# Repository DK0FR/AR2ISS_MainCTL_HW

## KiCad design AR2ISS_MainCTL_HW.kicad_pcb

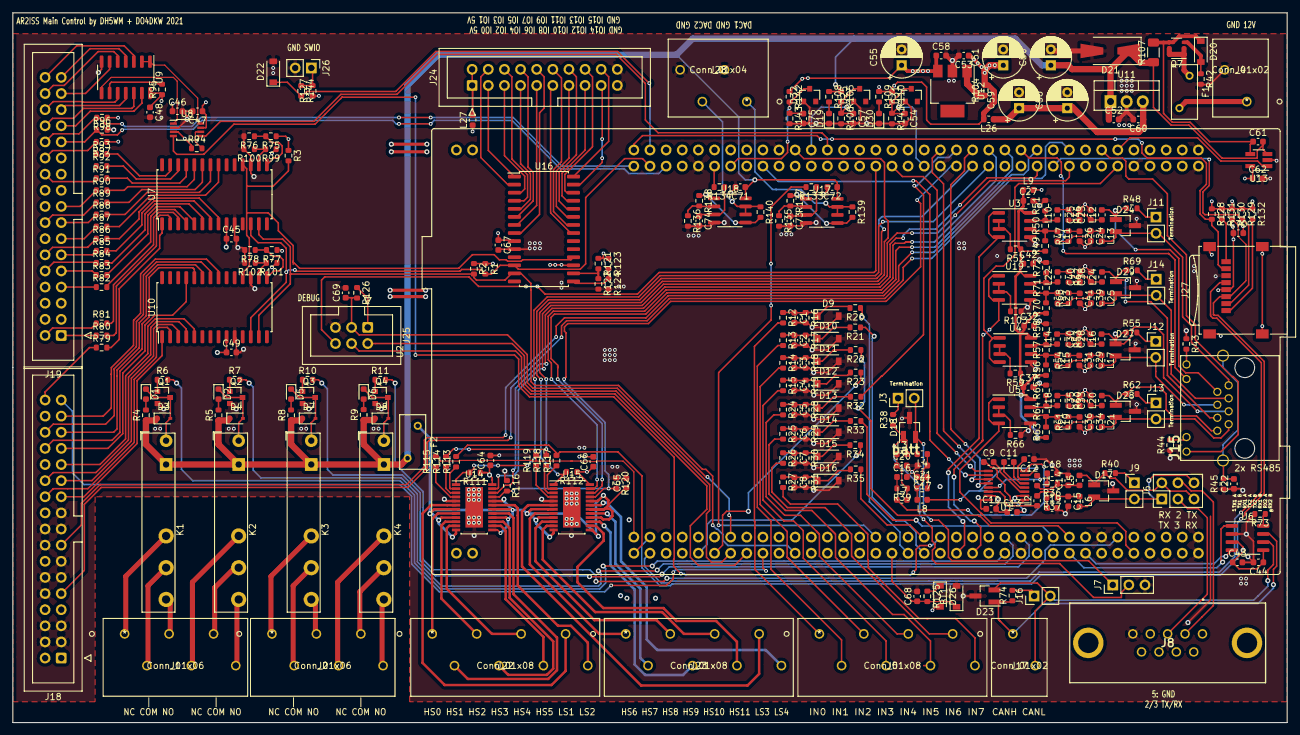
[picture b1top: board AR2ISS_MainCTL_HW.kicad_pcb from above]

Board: 4 copper layers, 200.7 x 111.8 mm, 333 parts (0 on the bottom side), 295 nets.

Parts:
BT1: Battery_Cell; D_SOD-123
C1, C2, C3, C4, C5, C6, C7, C8: 4,7n; C_0603_1608Metric
C9, C10, C11, C12, C13, C22, C27, C32, C37, C42, C45, C46, C47, C48, C49, C52, C53, C54, C57, C58, C60, C61, C62, C67, C75: 100n; C_0603_1608Metric
C14, C15, C20, C21, C23, C24, C28, C29, C33, C34, C38, C39: 470p; C_0603_1608Metric
C16, C17, C18, C19, C25, C26, C30, C31, C35, C36, C40, C41: 1n; C_0603_1608Metric
C43, C44, C64, C65, C66, C68, C69, C70, C71, C72, C73, C74: 100nF; C_0603_1608Metric
C50, C51, C55, C56, C59: 22u; CP_Radial_D6.3mm_P2.50mm
D1, D2, D5, D6, D19, D30: LED; LED_0603_1608Metric
D3, D4, D7, D8: 1N4148WS; D_SOD-323
D9, D10, D11, D12, D13, D14, D15, D16, D22: MMSZ3V6CW; D_SOD-123
D17, D18, D23, D24, D27, D28, D29: PESD2CAN; SOT-23_Handsoldering
D20: D_Zener; D_SOD-123
D21: D_TVS; D_SMA-SMB_Universal_Handsoldering
D25, D31, D32: BZX84C3V6,215; D_SOT-23_ANK
D26: BAT54W-HG3-08; D_SOD-123
F1, F2: PFRA 050; Fuse_BelFuse_0ZRE0005FF_L8.3mm_W3.8mm
J1, J2: Conn_01x06; 250-206
J3, J9, J11, J12, J13, J14, J16, J26: Conn_01x02; PinHeader_1x02_P2.54mm_Vertical
J4, J17: Conn_01x02; 250-202
J5, J22, J23: Conn_01x08; 250-208
J6: Conn_02x03_Odd_Even; PinHeader_2x03_P2.54mm_Vertical
J7: Conn_01x03; PinHeader_1x03_P2.54mm_Vertical
J8: DB9_Female; L177TSEH09SOL2RM8
J15: RJ45_LED
J18, J19: Conn_02x17_Odd_Even; IDC-Header_2x17_P2.54mm_Vertical
J24: Conn_02x10_Odd_Even; IDC-Header_2x10_P2.54mm_Vertical
J25: Conn_02x03_Odd_Even; IDC-Header_2x03_P2.54mm_Vertical
J27: Micro_SD_Card; microSD_HC_Wuerth_693072010801
J28: Conn_01x04; 250-204
K1, K2, K3, K4: FINDER-34.51; Relay_SPDT_Finder_34.51_Vertical
L1, L2, L7, L8, L10, L11, L14, L15, L18, L19, L22, L23: 10u; L_0603_1608Metric
L3, L4, L5, L6, L12, L13, L16, L17, L20, L21, L24, L25: 74279266; L_0603_1608Metric
L9, L26, L27: L; L_0603_1608Metric
Q1, Q2, Q3, Q4: BC846; SOT-23
Q7: PMN48XP; TSOP-6_1.65x3.05mm_P0.95mm
R1, R2, R3, R52, R59, R66, R75, R103, R121, R127: 4.7k; R_0603_1608Metric
R4, R5, R8, R9: 820; R_0603_1608Metric
R6, R7, R10, R11, R20, R21, R22, R23, R32, R33, R34, R35, R43, R44, R45, R133, R134, R142: 1k; R_0603_1608Metric
R12, R13, R14, R15, R24, R25, R26, R27: 56k; R_0603_1608Metric
R16, R17, R18, R19, R28, R29, R30, R31: 24k; R_0603_1608Metric
R36, R37, R39, R41, R46, R47, R53, R54, R60, R61, R67, R68: 221; R_0603_1608Metric
R38, R40, R48, R55, R62, R69, R74: 120; R_0603_1608Metric
R42, R109: 470; R_0603_1608Metric
R49, R50, R51, R56, R57, R58, R63, R64, R65, R70, R71, R72, R76, R77, R99, R101, R104, R111, R112, R116, R120, R122, R123, R139, R140: NB; R_0603_1608Metric
R73, R95, R96, R97, R98, R106, R110, R126: 10k; R_0603_1608Metric
R78, R100, R102, R124: 0R; R_0603_1608Metric
R79, R80, R81, R82, R83, R84, R85, R86, R87, R88, R89, R90, R91, R92, R93: 220; R_0603_1608Metric
R94: 3k; R_0603_1608Metric
R105: 82k; R_0603_1608Metric
R107: 0.1; R_1206_3216Metric_Pad1.30x1.75mm_HandSolder
R108: 1.5k; R_0603_1608Metric
R113, R114, R115, R117, R118, R119: 33; R_0603_1608Metric
R125, R144: 100R; R_0603_1608Metric
R128, R129, R130, R131, R132: 47k; R_0603_1608Metric
R135, R136: 8.2k; R_0603_1608Metric
R137, R138: 27k; R_0603_1608Metric
R141: 15k; R_0603_1608Metric
R143: 10meg; R_0603_1608Metric
U1: MAX3232; TSSOP-16_4.4x5mm_P0.65mm
U2: NUCLEO144-H745ZI; ST_Morpho_Connector_144_STLink
U3, U4, U5, U19: SP3485EN-L/TR; SOIC-8_3.9x4.9mm_P1.27mm
U6: MCP2562-E-SN; SOIC-8_3.9x4.9mm_P1.27mm
U7, U10, U16: MCP23017_SO; SOIC-28W_7.5x17.9mm_P1.27mm
U8: NTB0102DP; TSSOP-8_3x3mm_P0.65mm
U9: 74HC164; SOIC-14_3.9x8.7mm_P1.27mm
U11: LME78_05-1.0; TO-220-3_Vertical
U12: L78033; SOT-223
U13: TSC101B; SOT-23-5_HandSoldering
U14, U15: TLE75602-ESH; Infineon_PG-TSDSO-24-21
U17, U18: LM358; SOIC-8_3.9x4.9mm_P1.27mm

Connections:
+3V3: C10.1, C43.1, C44.1, C46.1, C55.1, C58.1, C64.1, C66.1, C70.1, D26.2, J25.1, J27.4, R94.1, R111.1, R112.1, R126.1, R127.1, R128.1, R129.1, R130.1, R131.1, R132.1, R142.1, U1.16, U6.3, U6.5, U8.3, U12.3, U14.24, U15.24
+5V: C45.1, C47.1, C48.1, C49.1, C51.1, C53.1, C62.1, C67.1, J18.7, J18.8, L9.2, L26.2, L27.1, R1.1, R2.1, R3.1, R75.1, R77.1, R95.1, R97.1, R98.1, R99.1, R101.1, R104.2, R109.1, R110.1, R121.1, R123.1, U2.6, U7.9, U8.7, U9.14, U10.9, U13.5, U16.9
+12V: C50.1, C52.1, C61.2, C71.1, C72.1, D3.1, D4.1, D7.1, D8.1, D21.1, F2.2, K1.A1, K2.A1, K3.A1, K4.A1, R4.1, R5.1, R8.1, R9.1, R105.1, R107.1, R108.1, U11.1, U13.3, U17.8, U18.8
+12VA: C65.1, F2.1, U14.7, U14.9, U14.12, U14.13, U14.16, U14.18, U14.20, U15.7, U15.9, U15.12, U15.13, U15.16, U15.18, U15.20
/ADIn/DA_IN_0: J5.1, R12.2
/ADIn/DA_IN_1: J5.2, R13.2
/ADIn/DA_IN_2: J5.3, R14.2
/ADIn/DA_IN_3: J5.4, R15.2
/ADIn/DA_IN_4: J5.5, R24.2
/ADIn/DA_IN_5: J5.6, R25.2
/ADIn/DA_IN_6: J5.7, R26.2
/ADIn/DA_IN_7: J5.8, R27.2
/ADIn/DA_IN_LL0: R20.1, U2.35
/ADIn/DA_IN_LL1: R21.1, U2.37
/ADIn/DA_IN_LL2: R22.1, U2.56
/ADIn/DA_IN_LL3: R23.1, U2.11
/ADIn/DA_IN_LL4: R32.1, U2.114
/ADIn/DA_IN_LL5: R33.1, U2.54
/ADIn/DA_IN_LL6: R34.1, U2.9
/ADIn/DA_IN_LL7: R35.1, U2.38
/AOut/DAC1: R133.2, U2.32
/AOut/DAC2: R134.2, U2.83
/CAN/FDCAN_RX: U2.57, U6.4
/CAN/FDCAN_TX: U2.55, U6.1
/Controller/#CS1: R111.2, U2.117, U14.1
/Controller/#CS2: R112.2, U2.115, U15.1
/Controller/ADC3V3: C75.1, D32.1, R142.2, R143.1, U2.85
/Controller/ADC5V: C54.1, D31.1, R110.2, R141.1, U2.109
/Controller/ADC12V: C57.1, D25.1, R105.2, R106.1, U2.96
/Controller/ADCPWR: U2.134, U13.1
/Controller/Backlight: J18.33, U2.17
/Controller/CD: J19.26, R98.2, U2.73
/Controller/CE: J19.25, R96.1, U2.77
/Controller/COM_RX1: U1.12, U2.116
/Controller/COM_RX2: U1.9, U2.105
/Controller/COM_TX1: U1.11, U2.112
/Controller/COM_TX2: U1.10, U2.89
/Controller/DisplayCLK: U2.40, U8.4
/Controller/DisplayData: U2.98, U8.5
/Controller/EN1: R116.2, R120.2, U2.113, U14.21, U15.21
/Controller/ENC_A: J18.15, U2.124
/Controller/ENC_B: J18.9, U2.128
/Controller/LD1: J15.12, U2.122
/Controller/LD2: J15.10, U2.132
/Controller/MISO: R115.2, R119.2, U2.2
/Controller/MOSI: R114.2, R118.2, U2.94
/Controller/NRST: C69.1, J25.3, R126.2, U2.14
/Controller/ONEWIRE: D22.1, R144.2, U2.76
/Controller/PWM_DOUT0: U2.127, U14.23
/Controller/PWM_DOUT1: U2.123, U14.22
/Controller/PWM_DOUT2: U2.118, U15.23
/Controller/PWM_DOUT3: U2.120, U15.22
/Controller/REL1: R6.2, U2.47
/Controller/REL2: R7.2, U2.48
/Controller/REL3: R10.2, U2.50
/Controller/REL4: R11.2, U2.62
/Controller/RX: U2.43, U19.1, U19.4
/Controller/RX2: U2.63, U5.1, U5.4
/Controller/SCL: R1.2, U2.75, U7.12, U10.12, U16.12
/Controller/SCLK: R113.2, R117.2, U2.1
/Controller/SDA: R2.2, U2.21, U7.13, U10.13, U16.13
/Controller/SWCLK: J25.4, U2.15
/Controller/SWDIO: J25.2, U2.13
/Controller/SWO: J25.6, U2.103
/Controller/TX: U2.41, U3.1, U3.4
/Controller/TX2: U2.133, U4.1, U4.4
/Controller/VBATT: BT1.1, C68.1, R125.2, U2.33
/DOut/IO0: J24.3, U16.1
/DOut/IO1: J24.4, U16.2
/DOut/IO2: J24.5, U16.3
/DOut/IO3: J24.6, U16.4
/DOut/IO4: J24.7, U16.5
/DOut/IO5: J24.8, U16.6
/DOut/IO6: J24.9, U16.7
/DOut/IO7: J24.10, U16.8
/DOut/IO8: J24.11, U16.21
/DOut/IO9: J24.12, U16.22
/DOut/IO10: J24.13, U16.23
/DOut/IO11: J24.14, U16.24
/DOut/IO12: J24.15, U16.25
/DOut/IO13: J24.16, U16.26
/DOut/IO14: J24.17, U16.27
/DOut/IO15: J24.18, U16.28
/DOut/RESET: R3.2, U7.18, U10.18, U16.18
/DOut/sheet60ADF1E9/A0: R123.2, R124.1, U16.15
/DOut/sheet60ADF1E9/A1: R121.2, R122.1, U16.16
/IOExpander2/A0: R77.2, R78.1, U10.15
/IOExpander2/A1: R101.2, R102.1, U10.16
/IOExpander/A0: R75.2, R76.1, U7.15
/IOExpander/A1: R99.2, R100.1, U7.16
/IOExpander/IO0: R79.2, U7.1
/IOExpander/IO1: R80.2, U7.2
/IOExpander/IO2: R81.2, U7.3
/IOExpander/IO3: R82.2, U7.4
/IOExpander/IO4: R83.2, U7.5
/IOExpander/IO5: R84.2, U7.6
/IOExpander/IO6: R85.2, U7.7
/IOExpander/IO7: R86.2, U7.8
/IOExpander/IO8: R87.2, U7.21
/IOExpander/IO9: R88.2, U7.22
/IOExpander/IO10: R89.2, U7.23
/IOExpander/IO11: R90.2, U7.24
/IOExpander/IO12: R91.2, U7.25
/IOExpander/IO13: R92.2, U7.26
/IOExpander/IO14: R93.2, U7.27
/LCD/BTN0: J18.21, U10.1
/LCD/BTN1: J18.22, U10.2
/LCD/BTN2: J18.23, U10.3
/LCD/BTN3: J18.24, U10.4
/LCD/BTN4: J18.25, U10.5
/LCD/BTN8: J18.31, U10.21
/LCD/BTN9: J18.30, U10.22
/LCD/BTN10: J18.29, U10.23
/LCD/BTN11: J18.28, U10.24
/LCD/BTN12: J18.27, U10.25
/LCD/D0: J19.34, U9.3
/LCD/D1: J19.33, U9.4
/LCD/D2: J19.32, U9.5
/LCD/D3: J19.31, U9.6
/LCD/D4: J19.30, U9.10
/LCD/D5: J19.29, U9.11
/LCD/D6: J19.28, U9.12
/LCD/D7: J19.27, U9.13
/LCD/LED1: J18.34, R79.1
/LCD/LED2: J19.1, R80.1
/LCD/LED3: J19.2, R81.1
/LCD/LED7: J19.7, R82.1
/LCD/LED11: J19.9, R83.1
/LCD/LED12: J19.10, R84.1
/LCD/LED13: J19.11, R85.1
/LCD/LED14: J19.12, R86.1
/LCD/LED15: J19.13, R87.1
/LCD/LED17: J19.15, R88.1
/LCD/LED18: J19.16, R89.1
/LCD/LED19: J19.17, R90.1
/LCD/LED22: J19.22, R91.1
/LCD/WR: J19.24, R97.2
/RS232/RS232Filter_1/A_ext: D17.1, J6.2, J6.5, L5.2, R40.1
/RS232/RS232Filter_1/A_int: L1.1, U1.13
/RS232/RS232Filter_1/B_ext: D17.2, J6.1, J6.6, J9.2, L6.2
/RS232/RS232Filter_1/B_int: L2.1, U1.14
/RS232/sheet608DD623/A_ext: D18.1, J7.2, L3.2, R38.1
/RS232/sheet608DD623/A_int: L7.1, U1.8
/RS232/sheet608DD623/B_ext: D18.2, J3.2, J7.1, L4.2
/RS232/sheet608DD623/B_int: L8.1, U1.7
/RS422/RS485Tranceiver1/A_in: D24.2, J11.2, J15.1, L13.2
/RS422/RS485Tranceiver1/B_in: D24.1, J15.2, L12.2, R48.1
/RS422/RS485Tranceiver1/DE1: R52.2, U3.2, U3.3
/RS422/RS485Tranceiver2/A_in: D29.2, J14.2, J15.3, L25.2
/RS422/RS485Tranceiver2/B_in: D29.1, J15.6, L24.2, R69.1
/RS422/RS485Tranceiver2/DE1: R103.2, U19.2, U19.3
/RS422/RS485Tranceiver3/A_in: D27.2, J12.2, J15.4, L17.2
/RS422/RS485Tranceiver3/B_in: D27.1, J15.5, L16.2, R55.1
/RS422/RS485Tranceiver3/DE1: R59.2, U4.2, U4.3
/RS422/RS485Tranceiver4/A_in: D28.2, J13.2, J15.7, L21.2
/RS422/RS485Tranceiver4/B_in: D28.1, J15.8, L20.2, R62.1
/RS422/RS485Tranceiver4/DE1: R66.2, U5.2, U5.3
/RS422/VCC_RS422: C27.1, C32.1, C37.1, C42.1, L9.1, R49.1, R52.1, R56.1, R59.1, R63.1, R70.1, U3.8, U4.8, U5.8, U19.8
/SDCard/#CD: J27.2, R129.2, U2.125
/SDCard/CLK: J27.5, U2.3
/SDCard/CMD: J27.3, R130.2, U2.4
/SDCard/D0: J27.7, R128.2, U2.74
GND: BT1.2, C1.2, C2.2, C3.2, C4.2, C5.2, C6.2, C7.2, C8.2, C10.2, C12.1, C13.1, C14.2, C15.2, C16.2, C17.2, C18.2, C19.2, C20.2, C21.2, C22.1, C23.2, C24.2, C25.2, C26.2, C27.2, C28.2, C29.2, C30.2, C31.2, C32.2, C33.2, C34.2, C35.2, C36.2, C37.2, C38.2, C39.2, C40.2, C41.2, C42.2, C43.2, C44.2, C45.2, C46.2, C47.2, C48.2, C49.2, C50.2, C51.2, C52.2, C53.2, C54.2, C55.2, C56.2, C57.2, C58.2, C59.2, C60.2, C62.2, C64.2, C65.2, C66.2, C67.2, C68.2, C69.2, C70.2, C71.2, C72.2, C73.2, C74.2, C75.2, D9.2, D10.2, D11.2, D12.2, D13.2, D14.2, D15.2, D16.2, D17.3, D18.3, D19.1, D21.2, D22.2, D23.3, D24.3, D25.2, D27.3, D28.3, D29.3, D30.1, D31.2, D32.2, J4.2, J7.3, J8.5, J18.3, J18.4, J18.5, J18.6, J18.10, J18.11, J18.12, J18.13, J18.16, J18.17, J18.18, J18.19, J24.19, J24.20, J25.5, J26.2, J27.6, J28.2, J28.4, Q1.2, Q2.2, Q3.2, Q4.2, R16.2, R17.2, R18.2, R19.2, R28.2, R29.2, R30.2, R31.2, R42.2, R43.1, R44.1, R45.1, R51.2, R58.2, R65.2, R66.1, R72.2, R73.2, R76.2, R78.2, R96.2, R100.2, R102.2, R103.1, R106.2, R116.1, R120.1, R122.2, R124.2, R135.2, R136.2, R141.2, R143.2, U1.15, U2.8, U2.19, U2.20, U2.22, U2.49, U2.60, U2.71, U2.72, U2.81, U2.92, U2.111, U2.126, U2.135, U2.143, U2.144, U3.5, U4.5, U5.5, U6.2, U7.10, U7.17, U8.2, U9.7, U10.10, U10.17, U11.2, U12.2, U13.2, U14.5, U14.25, U15.5, U15.25, U16.10, U16.17, U17.4, U18.4, U19.5
unnamed: C1.1, D9.1, R12.1, R16.1, R20.2
unnamed: C2.1, D10.1, R13.1, R17.1, R21.2
unnamed: C3.1, D11.1, R14.1, R18.1, R22.2
unnamed: C4.1, D12.1, R15.1, R19.1, R23.2
unnamed: C5.1, D13.1, R24.1, R28.1, R32.2
unnamed: C6.1, D14.1, R25.1, R29.1, R33.2
unnamed: C7.1, D15.1, R26.1, R30.1, R34.2
unnamed: C8.1, D16.1, R27.1, R31.1, R35.2
unnamed: C9.1, U1.1
unnamed: C9.2, U1.3
unnamed: C11.1, U1.4
unnamed: C11.2, U1.5
unnamed: C12.2, U1.6
unnamed: C13.2, U1.2
unnamed: C14.1, L1.2, L5.1, R36.1
unnamed: C15.1, L2.2, L6.1, R37.1
unnamed: C16.1, R39.2
unnamed: C17.1, R41.2
unnamed: C18.1, R36.2
unnamed: C19.1, R37.2
unnamed: C20.1, L3.1, L7.2, R39.1
unnamed: C21.1, L4.1, L8.2, R41.1
unnamed: C22.2, J15.13, R45.2
unnamed: C23.1, L10.2, L12.1, R46.1
unnamed: C24.1, L11.2, L13.1, R47.1
unnamed: C25.1, R46.2
unnamed: C26.1, R47.2
unnamed: C28.1, L14.2, L16.1, R53.1
unnamed: C29.1, L15.2, L17.1, R54.1
unnamed: C30.1, R53.2
unnamed: C31.1, R54.2
unnamed: C33.1, L18.2, L20.1, R60.1
unnamed: C34.1, L19.2, L21.1, R61.1
unnamed: C35.1, R60.2
unnamed: C36.1, R61.2
unnamed: C38.1, L22.2, L24.1, R67.1
unnamed: C39.1, L23.2, L25.1, R68.1
unnamed: C40.1, R67.2
unnamed: C41.1, R68.2
unnamed: C56.1, C59.1, C60.1, L26.1, U11.3
unnamed: C61.1, D20.1, Q7.4, R107.2, U13.4
unnamed: C73.1, R133.1, U17.3
unnamed: C74.1, R134.1, U18.3
unnamed: D1.1, D3.2, K1.A2, Q1.3
unnamed: D1.2, R4.2
unnamed: D2.1, D4.2, K2.A2, Q2.3
unnamed: D2.2, R5.2
unnamed: D5.1, D7.2, K3.A2, Q3.3
unnamed: D5.2, R8.2
unnamed: D6.1, D8.2, K4.A2, Q4.3
unnamed: D6.2, R9.2
unnamed: D19.2, R108.2
unnamed: D20.2, Q7.3, R42.1
unnamed: D23.1, J17.1, R74.1, U6.7
unnamed: D23.2, J16.2, J17.2, U6.6
unnamed: D26.1, R125.1
unnamed: D30.2, R109.2
unnamed: F1.1, Q7.1, Q7.2, Q7.5, Q7.6
unnamed: F1.2, J4.1
unnamed: J1.1, K1.12
unnamed: J1.2, K1.11
unnamed: J1.3, K1.14
unnamed: J1.4, K2.12
unnamed: J1.5, K2.11
unnamed: J1.6, K2.14
unnamed: J2.1, K3.12
unnamed: J2.2, K3.11
unnamed: J2.3, K3.14
unnamed: J2.4, K4.12
unnamed: J2.5, K4.11
unnamed: J2.6, K4.14
unnamed: J3.1, R38.2
unnamed: J6.3, J8.3
unnamed: J6.4, J8.2
unnamed: J9.1, R40.2
unnamed: J11.1, R48.2
unnamed: J12.1, R55.2
unnamed: J13.1, R62.2
unnamed: J14.1, R69.2
unnamed: J15.9, R44.2
unnamed: J15.11, R43.2
unnamed: J16.1, R74.2
unnamed: J22.1, U14.8
unnamed: J22.2, U14.17
unnamed: J22.3, U14.10
unnamed: J22.4, U14.15
unnamed: J22.5, U14.11
unnamed: J22.6, U14.14
unnamed: J22.7, U14.6
unnamed: J22.8, U14.19
unnamed: J23.1, U15.8
unnamed: J23.2, U15.17
unnamed: J23.3, U15.10
unnamed: J23.4, U15.15
unnamed: J23.5, U15.11
unnamed: J23.6, U15.14
unnamed: J23.7, U15.6
unnamed: J23.8, U15.19
unnamed: J24.1, J24.2, L27.2
unnamed: J26.1, R127.2, R144.1
unnamed: J27.1, R132.2
unnamed: J27.8, R131.2
unnamed: J28.1, R139.1, U17.6, U17.7
unnamed: J28.3, R140.1, U18.6, U18.7
unnamed: L10.1, R50.2, R51.1, U3.7
unnamed: L11.1, R49.2, R50.1, U3.6
unnamed: L14.1, R57.2, R58.1, U4.7
unnamed: L15.1, R56.2, R57.1, U4.6
unnamed: L18.1, R64.2, R65.1, U5.7
unnamed: L19.1, R63.2, R64.1, U5.6
unnamed: L22.1, R71.2, R72.1, U19.7
unnamed: L23.1, R70.2, R71.1, U19.6
unnamed: Q1.1, R6.1
unnamed: Q2.1, R7.1
unnamed: Q3.1, R10.1
unnamed: Q4.1, R11.1
unnamed: R73.1, U6.8
unnamed: R94.2, U8.6
unnamed: R95.2, U9.9
unnamed: R104.1, U12.1
unnamed: R113.1, U14.2
unnamed: R114.1, U14.3
unnamed: R115.1, U14.4
unnamed: R117.1, U15.2
unnamed: R118.1, U15.3
unnamed: R119.1, U15.4
unnamed: R135.1, R137.2, U17.2
unnamed: R136.1, R138.2, U18.2
unnamed: R137.1, R139.2, U17.1, U17.5
unnamed: R138.1, R140.2, U18.1, U18.5
unnamed: U8.1, U9.8
unnamed: U8.8, U9.1, U9.2

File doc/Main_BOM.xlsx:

Designator | Quantity | Value | Footprint | LCSC Part # | Mouser | Spalte1
BT1 | 1 | Battery_Cell | Diode_SMD:D_SOD-123
C1 C2 C3 C4 C5 C6 C7 C8 | 8 | 4,7n | Capacitor_SMD:C_0603_1608Metric | C53987
C14 C15 C20 C21 C23 C24 C28 C29 C33 C34 C38 C39 | 12 | 470p | Capacitor_SMD:C_0603_1608Metric | C1620
C16 C17 C18 C19 C25 C26 C30 C31 C35 C36 C40 C41 | 12 | 1n | Capacitor_SMD:C_0603_1608Metric | C1620
C43 C44 C63 C64 C65 C66 C68 C69 C70 C71 C72 C73 C74 | 13 | 100nF | Capacitor_SMD:C_0603_1608Metric | C14663
C50 C51 C55 C56 C59 | 5 | 22u | Capacitor_THT:CP_Radial_D6.3mm_P2.50mm
C9 C10 C11 C12 C13 C22 C27 C32 C37 C42 C45 C46 C47 C48 C49 C52 C53 C54 C57 C58 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 | 25 | 100n | Capacitor_SMD:C_0603_1608Metric | C14663
D19 D30 | 2 | LED G | LED_SMD:LED_0603_1608Metric | C72043
D1 D2 D5 D6 | 4 | LED R | LED_SMD:LED_0603_1608Metric | C2286
D17 D18 D23 D24 D27 D28 D29 | 7 | PESD2CAN | Package_TO_SOT_SMD:SOT-23_Handsoldering | C32677
D20 | 1 | D_Zener | Diode_SMD:D_SOD-123 |  |  | xx
D21 | 1 | D_TVS | Diode_SMD:D_SMA-SMB_Universal_Handsoldering |  |  | xx
D25 D31 D32 | 3 | BZX84Cxx | Diode_SMD:D_SOT-23_ANK | C96230
D26 | 1 | D_Schottky | Diode_SMD:D_SOD-123 | C8598
D3 D4 D7 D8 | 4 | 1N4148WS | Diode_SMD:D_SOD-323 | C2128
D9 D10 D11 D12 D13 D14 D15 D16 D22 | 9 | MMSZ3V6CW | Diode_SMD:D_SOD-123 | C169493
F1 F2 | 2 | PFRA 050 | Fuse:Fuse_BelFuse_0ZRE0005FF_L8.3mm_W3.8mm |  | PFRA.050
J1 J2 | 2 | Conn_01x06 | AR2ISS:250-206 |  |  | xx
J15 | 1 | RJ45_LED | AR2ISS:RJ45_LED |  |  | stock
J4 J17 | 2 | Conn_01x02 | AR2ISS:250-202 |  |  | xx
J18 J19 | 2 | Conn_02x17_Odd_Even | Connector_IDC:IDC-Header_2x17_P2.54mm_Vertical |  |  | xx
J5 J22 J23 | 3 | Conn_01x08 | AR2ISS:250-208 |  |  | xx
J24 | 1 | Conn_02x10_Odd_Even | Connector_IDC:IDC-Header_2x10_P2.54mm_Vertical |  |  | xx
J25 | 1 | Conn_02x03_Odd_Even | Connector_IDC:IDC-Header_2x03_P2.54mm_Vertical |  |  | xx
J27 | 1 | Micro_SD_Card |  |  |  | xx
J28 | 1 | Conn_01x04
J6 | 1 | Conn_02x03_Odd_Even | Connector_PinHeader_2.54mm:PinHeader_2x03_P2.54mm_Vertical |  |  | xx
J7 | 1 | Conn_01x03 |  |  |  | xx
J8 | 1 | DB9_Female | AR2ISS:L177TSEH09SOL2RM8 |  | 523-TSEH09SOL2RM8
J3 J9 J11 J12 J13 J14 J16 J26 | 8 | Conn_01x02 | Connector_PinHeader_2.54mm:PinHeader_1x02_P2.54mm_Vertical |  |  | xx
JP1 JP2 | 2 | Jumper_NO_Small
K1 K2 K3 K4 | 4 | FINDER-34.51 | Relay_THT:Relay_SPDT_Finder_34.51_Vertical |  |  | xx
L1 L2 L7 L8 L10 L11 L14 L15 L18 L19 L22 L23 | 12 | 10u | Inductor_SMD:L_0603_1608Metric | C1035
L9 L26 L27 | 3 | L | Inductor_SMD:L_0603_1608Metric |  | 81-BLM18KG102SN1D
L3 L4 L5 L6 L12 L13 L16 L17 L20 L21 L24 L25 | 12 | 74279266 | Inductor_SMD:L_0603_1608Metric | C85824
Q1 Q2 Q3 Q4 | 4 | BC846 | Package_TO_SOT_SMD:SOT-23 | C20526
Q7 | 1 | PMN48XP | Package_SO:TSOP-6_1.65x3.05mm_P0.95mm |  | 771-PMN48XP115
R104 R139 R140 | 3 | NB | Resistor_SMD:R_0603_1608Metric
R105 | 1 | 82k | Resistor_SMD:R_0603_1608Metric | C23254
R107 | 1 | 0.1 | Resistor_SMD:R_1206_3216Metric_Pad1.30x1.75mm_HandSolder |  | KDV12DR100ET
R108 | 1 | 1.5k | Resistor_SMD:R_0603_1608Metric | C22843
R113 R114 R115 R117 R118 R119 | 6 | 33 | Resistor_SMD:R_0603_1608Metric | C23140
R111 R112 R116 R120 | 4 | 100k | Resistor_SMD:R_0603_1608Metric | C25803
R12 R13 R14 R15 R24 R25 R26 R27 | 8 | 56k | Resistor_SMD:R_0603_1608Metric | C23206
R125 | 1 | 100R | Resistor_SMD:R_0603_1608Metric | C22775
R127 | 1 | 4k7 | Resistor_SMD:R_0603_1608Metric | C23162
R128 R129 R130 R131 R132 | 5 | 47k | Resistor_SMD:R_0603_1608Metric | C25819
R135 R136 | 2 | 8.2k | Resistor_SMD:R_0603_1608Metric | C25981
R137 R138 | 2 | 27k | Resistor_SMD:R_0603_1608Metric | C22967
R141 | 1 | 15k | Resistor_SMD:R_0603_1608Metric | C22809
R143 | 1 | 10meg | Resistor_SMD:R_0603_1608Metric | C7250
R144 | 1 | 100 |  | C22775
R16 R17 R18 R19 R28 R29 R30 R31 | 8 | 24k | Resistor_SMD:R_0603_1608Metric | C23352
R1 R2 R3 R75 R100 R78 R102 R121 R124 | 3 | 4.7k | Resistor_SMD:R_0603_1608Metric | C23162
R36 R37 R39 R41 R46 R47 R53 R54 R60 R61 R67 R68 | 12 | 221 | Resistor_SMD:R_0603_1608Metric | C22962
R4 R5 R8 R9 | 4 | 820 | Resistor_SMD:R_0603_1608Metric | C25981
R38 R40 R48 R55 R62 R69 R74 | 7 | 120 | Resistor_SMD:R_0603_1608Metric | C22787
R42 R109 | 2 | 470 | Resistor_SMD:R_0603_1608Metric | C23179
R6 R7 R10 R11 R20 R21 R22 R23 R32 R33 R34 R35 R43 R44 R45 R50 R57 R64 R71 R133 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 | 22 | 1k | Resistor_SMD:R_0603_1608Metric | C21190
R49 R51 R56 R58 R63 R65 R70 R72 R73 R95 R96 R97 R98 R106 R110 R126 | 16 | 10k | Resistor_SMD:R_0603_1608Metric | C25804
R76 R77 R99 R101 R122 R123 | 12 | R | Resistor_SMD:R_0603_1608Metric
R79 R80 R81 R82 R83 R84 R85 R86 R87 R88 R89 R90 R91 R92 R93 | 15 | 220 | Resistor_SMD:R_0603_1608Metric | C22962
R52 R59 R66 R94 R103 | 5 | 3k | Resistor_SMD:R_0603_1608Metric | C4211
U1 | 1 | MAX3232 | Package_SO:TSSOP-16_4.4x5mm_P0.65mm |  | 700-MAX3232EUET
U11 | 1 | LME78_05-1.0 | Package_TO_SOT_THT:TO-220-3_Vertical |  | TSR 1-2450E
U12 | 1 | L78033 | Package_TO_SOT_SMD:SOT-223 |  | UA78M33CDCYR
U13 | 1 | TSC101B | Package_TO_SOT_SMD:SOT-23-5_HandSoldering |  | TSC101BIYLT
U14 U15 | 2 | TLE75602-ESH | AR2ISS:Infineon_PG-TSDSO-24-21 |  | TLE75602-ESH
U17 U18 | 2 | LM358 | Package_SO:SOIC-8_3.9x4.9mm_P1.27mm |  | C7950
U2 | 1 | NUCLEO144-H745ZI | Module:ST_Morpho_Connector_144_STLink | 511-NUCLEO-H755ZI-Q
U3 U4 U5 U19 | 4 | SN75176AD | Package_SO:SOIC-8_3.9x4.9mm_P1.27mm | C8963
U6 | 1 | MCP2562-E-SN | Package_SO:SOIC-8_3.9x4.9mm_P1.27mm |  | Not Avaiable
U7 U10 U16 | 3 | MCP23017_SO | Package_SO:SOIC-28W_7.5x17.9mm_P1.27mm | C47023
U8 | 1 | TXB0102DCT | Package_SO:TSSOP-8_3x3mm_P0.65mm |  | NTB0102DP-Q100H
U9 | 1 | 74HC164 | Package_SO:SOIC-14_3.9x8.7mm_P1.27mm | C6825

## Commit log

2021-03-28 inital commit
2021-04-07 add RS422, RS232 filters
2021-04-11 add SDcard, OneWire, Batt, analog out, digital out
2021-04-21 start placement
2021-04-26 placement
2021-05-14 add TLE5602
2021-05-15 added bom
2021-05-15 updated bom
2021-05-15 added all part no
2021-05-16 routing
2021-05-17 placement, routing
2021-05-20 ready for jlc
2021-05-20 final routing
2021-05-20 updated production files
2021-05-20 Revert "Merge branch 'main' of https://github.com/DK0FR/AR2ISS_MainCTL_HW into main"
    This reverts commit 84b496f7dd10a9c74f40f7184d52c03f26cb2fa9, reversing
    changes made to 60feb35f0dc9db917dd5d2edb20ef986b7636c97.

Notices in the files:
parts and their libraries:
Copyright 2016 Accelerated Designs. All rights reserved.
